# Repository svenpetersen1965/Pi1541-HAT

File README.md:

# Pi1541-HAT
Just another Pi1541-HAT. Please refer to Steve Whites project page (https://cbm-pi1541.firebaseapp.com/), who had the idea for the project and develops the software running in the Raspberry Pi.

There are several Pi1541-HATs, which are all good, nevertheless I have decided to make my own HAT. 

1. It has detachable display, switches and IEC-Bus boards

2. There is a barrel connector on the IEC-Bus Board, so no requirement for using the micro USB and no side entry for the enclosure required.

Find some info on the required cable making <a href="http://tech.guitarsite.de/cable_making.html">on my website</a>

I have made it this way to add flexibility to the HAT when it comes to be installed in an enclose and also alows a lower profile enclosure, since the high IEC-bus jacks are not above HAT level.

As a replacement for the switch board, a pcb with a rotary encoder with push button has been developed. This adds a quite bit more comfort while navigating through the directories. It mimiks the select, up and down button. This way, it works with the regular firmware (even before 1.21). Depending on the amount of text to be scrolled on the display, some pulses might get lost, which is hard to notice and does not reduce the usability.

The kernal revision v1.21 supports the connection of a rotary encoder. Rev. 2 of the HAT PCB provides the connection of a rotary encoder module (KY-040), which is widely available on ebay etc. This is ment to be as a cheaper alternative for the otary encoder board of this project. 

The Rev. 2 of HAT and Switch and the (newest) Rev. 1 of the IEC board were tested and are fully functional.

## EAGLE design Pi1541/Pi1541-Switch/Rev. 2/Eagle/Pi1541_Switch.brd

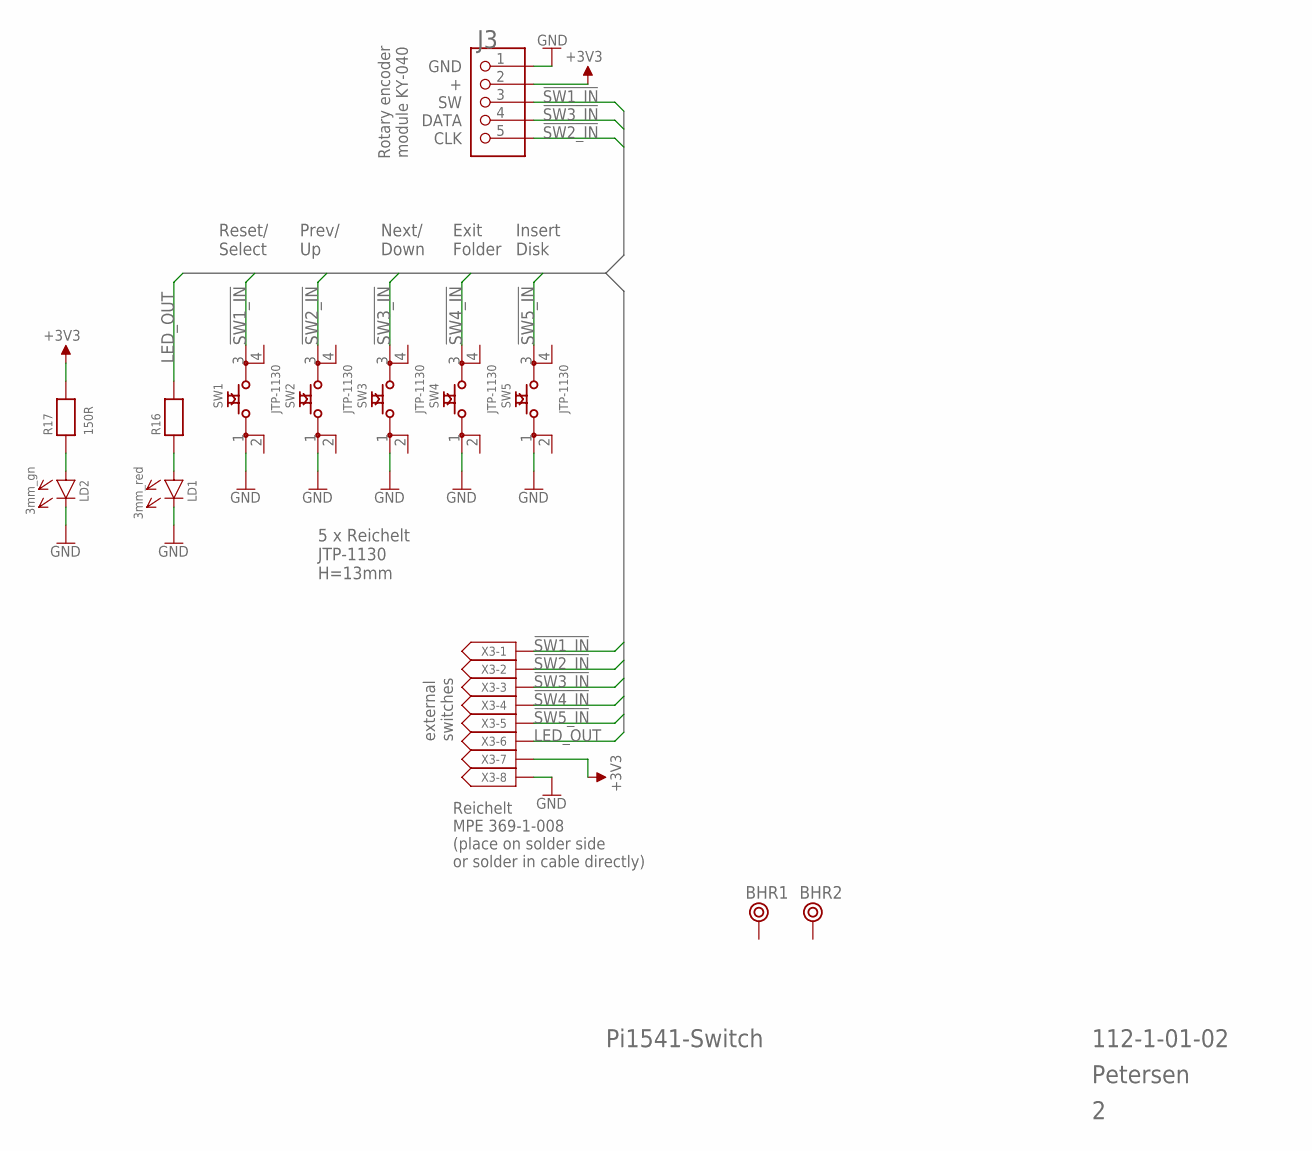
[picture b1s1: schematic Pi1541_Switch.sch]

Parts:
BHR1, BHR2: BOHR2,8; BOHR2,8_
J3: PINHD-1X5; 1X05
LD1: 3mm_red; 3MM
LD2: 3mm_gn; 3MM
R16, R17: 150R; 0805
SW1, SW2, SW3, SW4, SW5: JTP-1130
X3: MICMA08B

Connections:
!SW1_IN: J3.3, SW1.3, X3.1
!SW2_IN: J3.5, SW2.3, X3.2
!SW3_IN: J3.4, SW3.3, X3.3
!SW4_IN: SW4.3, X3.4
!SW5_IN: SW5.3, X3.5
+3V3: J3.2, R17.2, X3.7
GND: J3.1, LD1.C (K), LD2.C (K), SW1.1, SW2.1, SW3.1, SW4.1, SW5.1, X3.8
LED_OUT: R16.2, X3.6
unnamed: LD2.A, R17.1
unnamed: LD1.A, R16.1

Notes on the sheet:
5 x Reichelt JTP-1130 H=13mm
Reset/ Select
Prev/ Up
Next/ Down
Exit Folder
Insert Disk
external switches
Reichelt MPE 369-1-008 (place on solder side or solder in cable directly)
Pi1541-Switch
Petersen
112-1-01-02
GND
DATA
CLK
Rotary encoder module KY-040

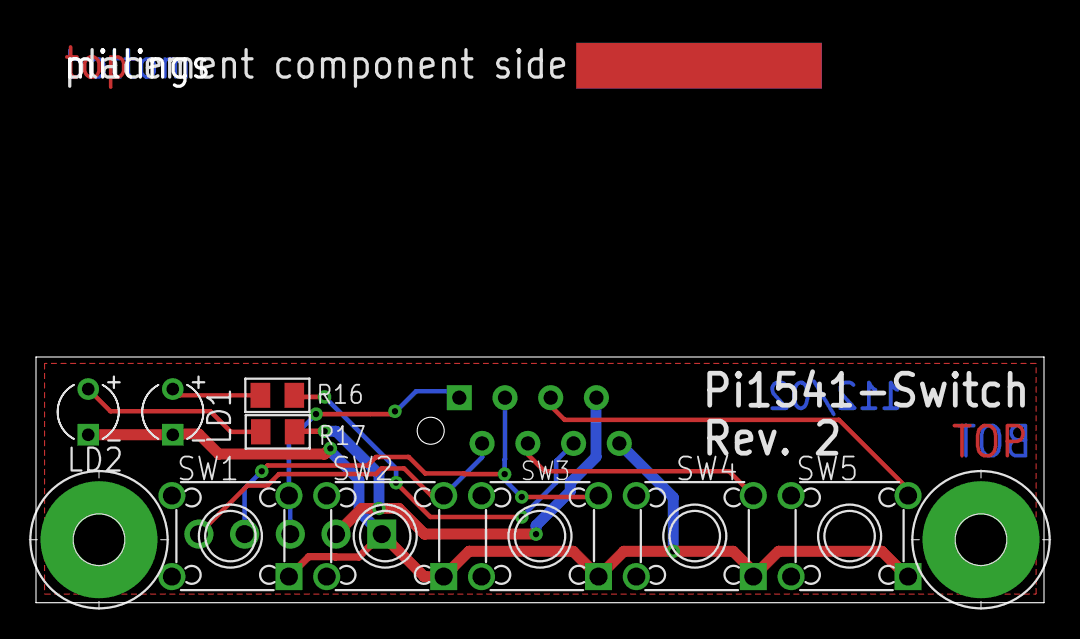
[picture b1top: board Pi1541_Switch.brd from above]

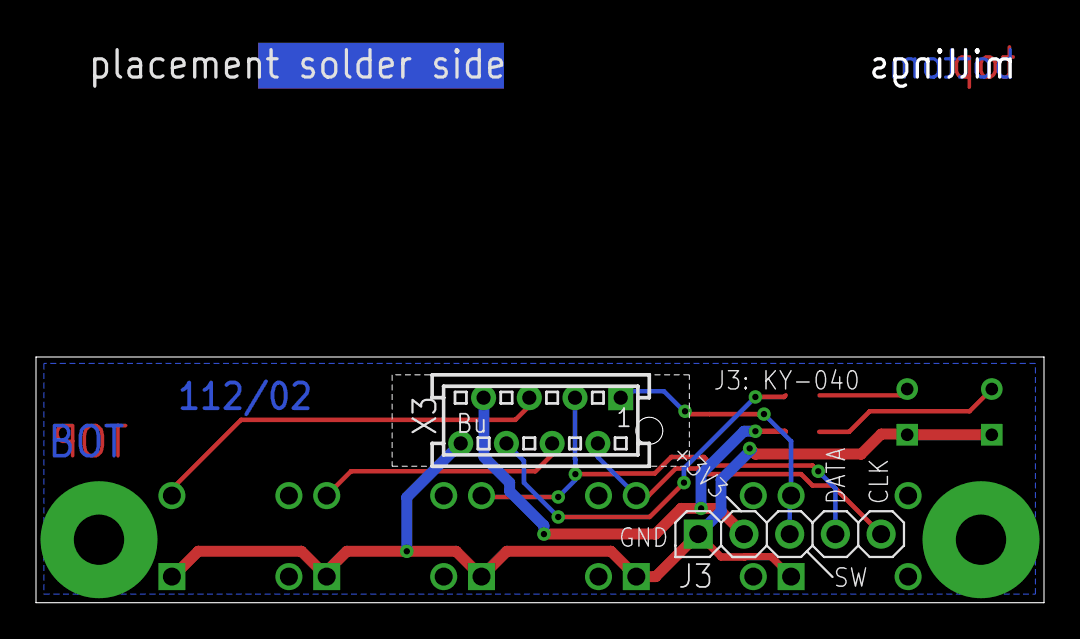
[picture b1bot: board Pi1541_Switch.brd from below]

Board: 2 copper layers, 56.0 x 31.5 mm, 15 parts (2 on the bottom side), 10 nets.

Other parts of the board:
U$44: 2LAYER
U$45: PCB-TITLE/

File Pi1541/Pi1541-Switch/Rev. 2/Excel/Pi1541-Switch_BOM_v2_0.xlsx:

Pi1541-Switch Rev. 2
Bill of Material Rev. 2.0
Pos. | Qty | Value | Footprint | Ref.-No. | Comment
1 | 1 | 112-2-01-02 | 2 Layers | PCB Rev. 2 | 2 layers, Cu 35µ, HASL, 13.65mm x 56.0mm, 1.6mm FR4
2 | 1 | 369-1-008 | MICMA08B | X3 | MPE Garry, Reichel MPE 369-1-008, Micromatch, female, tht, 8 pin
3 | 2 | 150R | 0805 | R16, R17 | resistor
4 | 1 | 3mm_gn | 3MM | LD2 | LED, 3mm, green
5 | 1 | 3mm_red | 3MM | LD1 | LED, 3mm, red
6 | 5 | JTP-1130D | JTP-1130 | SW1, SW2, SW3, SW4, SW5 | Namae Electronics, Reichelt JTP-1130, H=13mm
7 | 1 | 1x5p, pitch 2.54mm |  | J3 | Optional for rotary encoder (KY-040 etc.), standard pin header. Replaces SW1, S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
Pos. |  | Rev. 1 ® Rev. 2
1 |  | PCB revision
7 |  | new

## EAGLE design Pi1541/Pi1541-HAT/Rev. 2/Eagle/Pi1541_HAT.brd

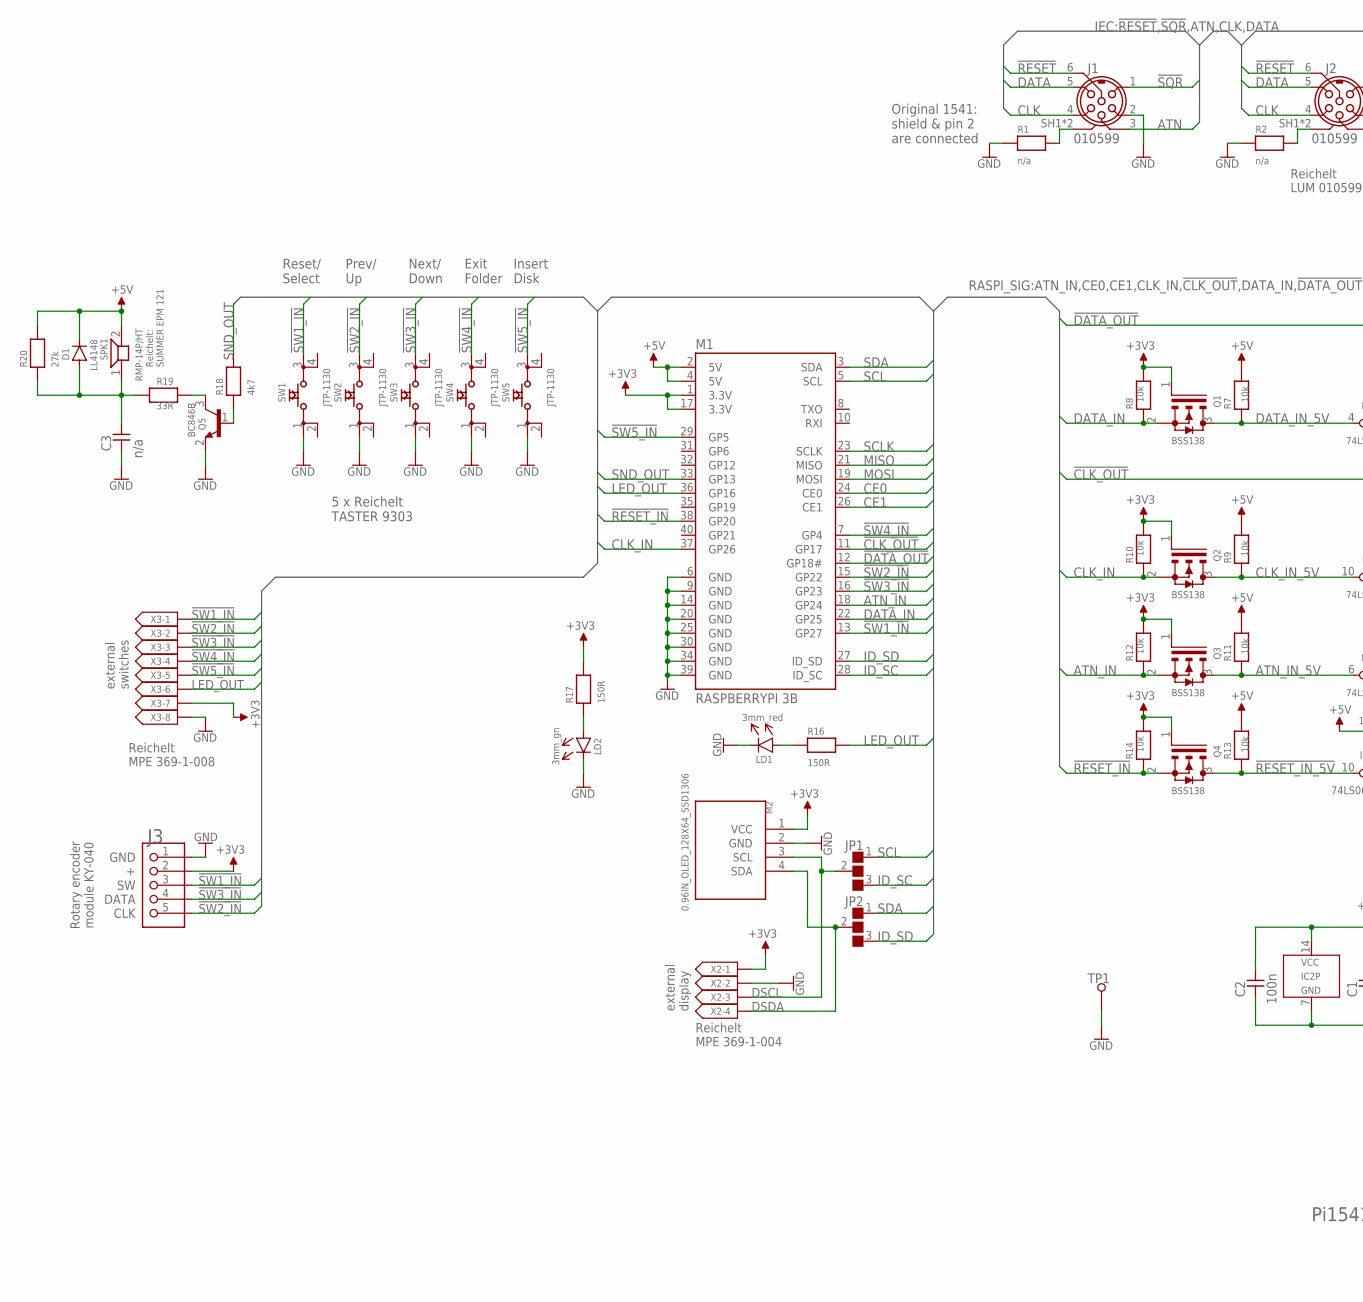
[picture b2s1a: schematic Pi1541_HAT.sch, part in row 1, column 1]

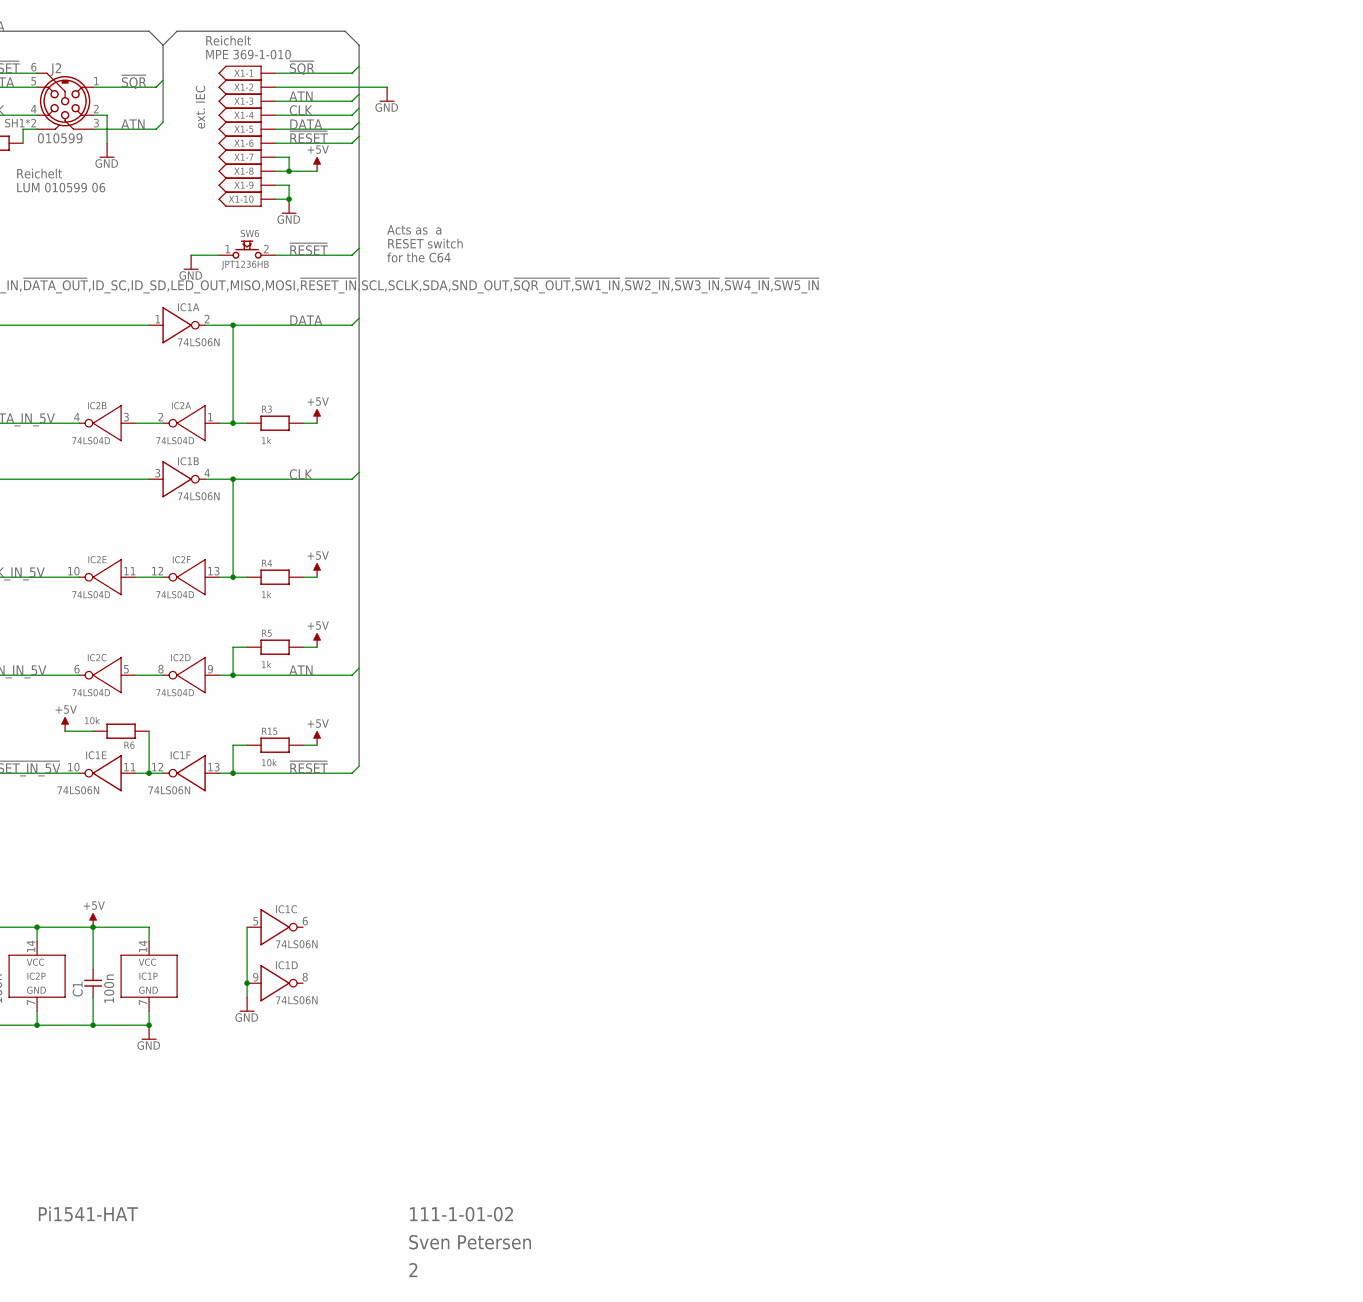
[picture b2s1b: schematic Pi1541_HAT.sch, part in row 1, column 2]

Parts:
C1, C2: 100n; 0805
C3: n/a; 0805
D1: LL4148; SOD80C
IC1: 74LS06N; DIL-14
IC2: 74LS04D; SO-14
J1, J2: 010599
J3: PINHD-1X5; 1X05
JP1, JP2: JMP_0603; CP3P
LD1: 3mm_red; 3MM
LD2: 3mm_gn; 3MM
M1: RASPBERRYPI 3B; PI_HAT_40P
M2: 0.96IN_OLED_128X64_SSD1306; OLED_0.96_SSD1306
Q1, Q2, Q3, Q4: BSS138; SOT23
Q5: BC846B; SOT23
R1, R2: n/a; 0805
R3, R4, R5: 1k; 0805
R6, R7, R8, R9, R10, R11, R12, R13, R14, R15: 10k; 0805
R16, R17: 150R; 0805
R18: 4k7; 0805
R19: 33R; 0805
R20: 27k; 0805
SPK1: RMP-14P/HT
SW1, SW2, SW3, SW4, SW5: JTP-1130
SW6: JPT1236HB; JTP_1236HB
TP1: L1,2_R; 1,2MM_R
X1: 369-1-010; MICMA10B
X2: 369-1-004; MICMA04B
X3: 369-1-008; MICMA08B

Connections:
!CLK_OUT: IC1.3 (I), M1.11 (GP17)
!DATA_OUT: IC1.1 (I), M1.12 (GP18#)
!RESET: IC1.13 (I), J1.6, J2.6, R15.1, SW6.2, X1.6
!RESET_IN: M1.38 (GP20), Q4.2 (S), R14.1
!RESET_IN_5V: IC1.10 (O), Q4.3 (D), R13.1
!SQR: J1.1, J2.1, X1.1
!SW1_IN: J3.3, M1.13 (GP27), SW1.3, X3.1
!SW2_IN: J3.5, M1.15 (GP22), SW2.3, X3.2
!SW3_IN: J3.4, M1.16 (GP23), SW3.3, X3.3
!SW4_IN: M1.7 (GP4), SW4.3, X3.4
!SW5_IN: M1.29 (GP5), SW5.3, X3.5
+3V3: J3.2, M1.1 (3.3V), M1.17 (3.3V), M2.1 (VCC), Q1.1 (G), Q2.1 (G), Q3.1 (G), Q4.1 (G), R8.2, R10.2, R12.2, R14.2, R17.2, X2.1, X3.7
+5V: C1.2, C2.2, D1.K, IC1.14 (VCC), IC2.14 (VCC), M1.2 (5V), M1.4 (5V), R3.2, R4.2, R5.2, R6.2, R7.2, R9.2, R11.2, R13.2, R15.2, R20.2, SPK1.2, X1.7, X1.8
ATN: IC2.9 (I), J1.3, J2.3, R5.1, X1.3
ATN_IN: M1.18 (GP24), Q3.2 (S), R12.1
ATN_IN_5V: IC2.6 (O), Q3.3 (D), R11.1
CE0: M1.24 (CE0)
CE1: M1.26 (CE1)
CLK: IC1.4 (O), IC2.13 (I), J1.4, J2.4, R4.1, X1.4
CLK_IN: M1.37 (GP26), Q2.2 (S), R10.1
CLK_IN_5V: IC2.10 (O), Q2.3 (D), R9.1
DATA: IC1.2 (O), IC2.1 (I), J1.5, J2.5, R3.1, X1.5
DATA_IN: M1.22 (GP25), Q1.2 (S), R8.1
DATA_IN_5V: IC2.4 (O), Q1.3 (D), R7.1
DSCL: JP1.2, M2.3 (SCL), X2.3
DSDA: JP2.2, M2.4 (SDA), X2.4
GND: C1.1, C2.1, C3.1, IC1.5 (I), IC1.7 (GND), IC1.9 (I), IC2.7 (GND), J1.2, J2.2, J3.1, LD1.K, LD2.K, M1.6 (GND), M1.9 (GND), M1.14 (GND), M1.20 (GND), M1.25 (GND), M1.30 (GND), M1.34 (GND), M1.39 (GND), M2.2 (GND), Q5.2 (E), R1.1, R2.1, SW1.1, SW2.1, SW3.1, SW4.1, SW5.1, SW6.1, TP1.1, X1.2, X1.9, X1.10, X2.2, X3.8
ID_SC: JP1.3, M1.28 (ID_SC)
ID_SD: JP2.3, M1.27 (ID_SD)
LED_OUT: M1.36 (GP16), R16.2, X3.6
MISO: M1.21 (MISO)
MOSI: M1.19 (MOSI)
unnamed: J1.SH1 (SH), J1.SH2 (SH), R1.2
unnamed: J2.SH1 (SH), J2.SH2 (SH), R2.2
unnamed: IC2.2 (O), IC2.3 (I)
unnamed: IC2.11 (I), IC2.12 (O)
unnamed: IC2.5 (I), IC2.8 (O)
unnamed: IC1.11 (I), IC1.12 (O), R6.1
unnamed: LD2.A, R17.1
unnamed: Q5.1 (B), R18.1
unnamed: Q5.3 (C), R19.2
unnamed: C3.2, D1.A, R19.1, R20.1, SPK1.1
unnamed: LD1.A, R16.1
SCL: JP1.1, M1.5 (SCL)
SCLK: M1.23 (SCLK)
SDA: JP2.1, M1.3 (SDA)
SND_OUT: M1.33 (GP13), R18.2

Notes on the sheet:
Original 1541: shield & pin 2 are connected
5 x Reichelt TASTER 9303
Reset/ Select
Prev/ Up
Next/ Down
Exit Folder
Insert Disk
Reichelt: SUMMER EPM 121
external display
external switches
Acts as a RESET switch for the C64
Reichelt MPE 369-1-004
Reichelt MPE 369-1-008
Reichelt MPE 369-1-010
ext. IEC
Reichelt LUM 010599 06
Pi1541-HAT
Sven Petersen
111-1-01-02
GND
DATA
CLK
Rotary encoder module KY-040

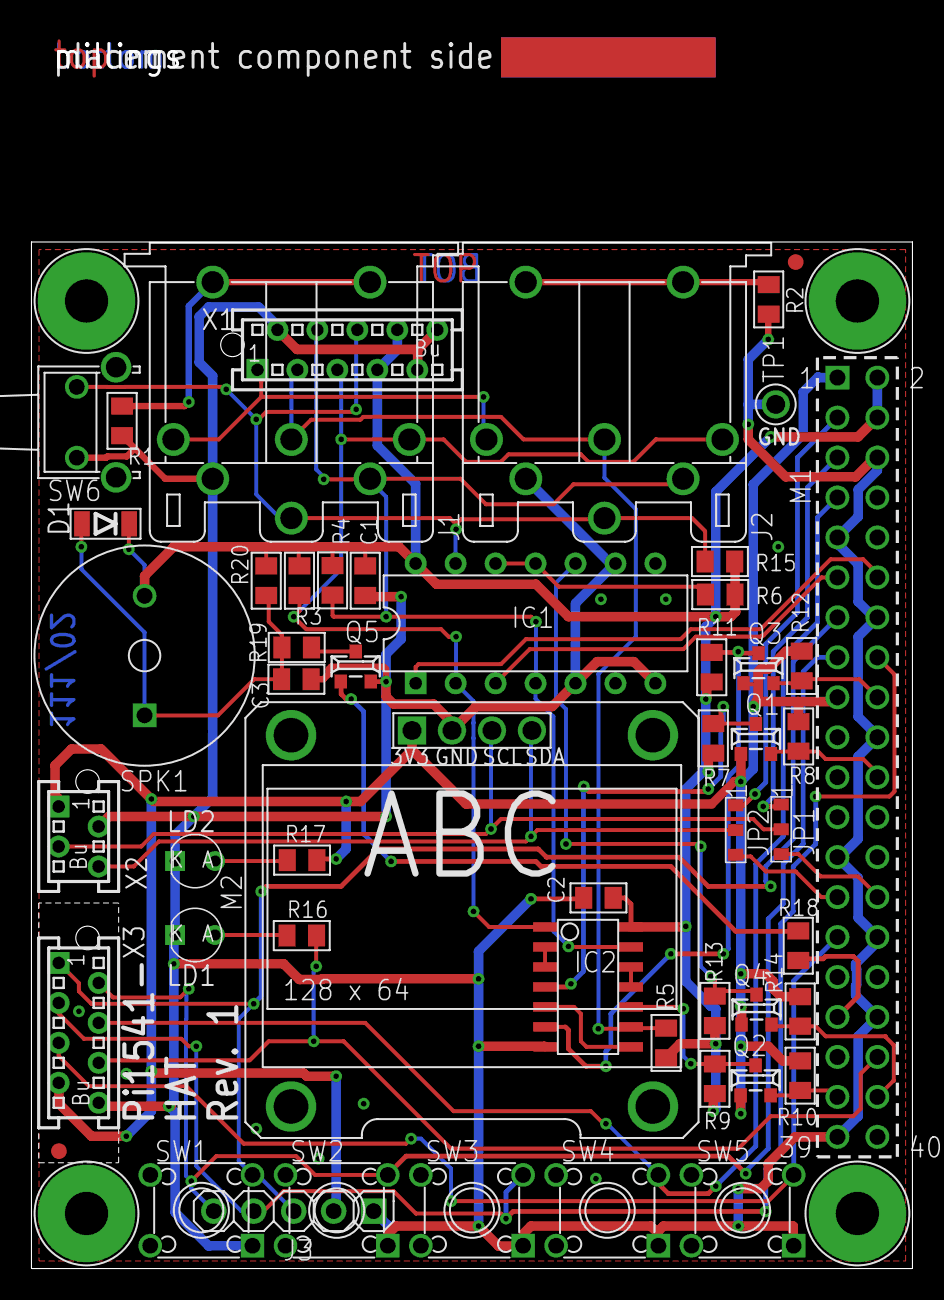
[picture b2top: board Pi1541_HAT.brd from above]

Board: 2 copper layers, 56.0 x 78.6 mm, 55 parts (0 on the bottom side), 42 nets.

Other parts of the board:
U$44: 2LAYER
U$45: PCB-TITLE/
U$47, U$48: SMD_REF_R1MM

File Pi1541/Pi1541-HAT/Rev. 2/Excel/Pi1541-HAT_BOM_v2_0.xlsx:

Pi1541-HAT Rev. 2
Bill of Material Rev. 2.0
Pos. | Qty | Value | Footprint | Ref.-No. | Comment
1 | 1 | 111-2-01-02 | 2 Layer | PCB Rev. 2 | 2 layer, Cu 35µ, HASL, 56.0mm x 65.25mm, 1.6mm FR4
2 | 1 | 369-1-008 | MICMA08B | X3 | MicroMatch MPE, e.g. Reichelt MPE 369-1-008
3 | 1 | 372-1-008 |  | (X3) | option: MicroMatch MPE, e.g. Reichelt MPE 372-1-008
4 | 1 | 0.96IN_OLED_128X64_SSD1306 | OLED_0.96_SSD1306 | M2 | 0.96" OLED Display 128x64, controller: SSD1306 or 1.3" OLED Display 128x64, con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
5 | 1 | 115-1-004 |  | (M2) | option: MPE Garry, e.g. Reichelt MPE 115-1-004
6 | 2 | 010599 | 10599 | J1, J2 | Lumberg, e.g. Reichelt 010599 06
7 | 3 | 100n | 0805 | C1, C2, C3
8 | 10 | 10k | 0805 | R6, R7, R8, R9, R10, R11, R12, R13, R14, R15
9 | 2 | 150R | 0805 | R16, R17
10 | 3 | 1k | 0805 | R3, R4, R5
11 | 1 | 33R | 0805 | R19
12 | 1 | 3mm_gn | 3MM | LD2 | LED 3mm, green
13 | 1 | 3mm_red | 3MM | LD1 | LED 3mm, red
14 | 1 | 74LS04D | SO-14 | IC2
15 | 1 | 74LS06N | DIL-14 | IC1
16 | 1 | BC846B | SOT23 | Q5
17 | 4 | BSS138 | SOT23 | Q1, Q2, Q3, Q4
18 | 2 | JMP_0603 | CP3P | JP1, JP2 | Jumper, default: 0R/0603 (1-2)
19 | 2 | 0R | 0603 | (JP1), (JP2)
20 | 1 | JPT1236HB | JTP_1236HB | SW6 | Namae Electronics, e.g. Reichelt TASTER 3305B
21 | 5 | JTP-1130 | JTP-1130 | SW1, SW2, SW3, SW4, SW5 | Namae Electronics, e.g. Reichelt TASTER 9303
22 | 1 | LL4148 | SOD80C | D1 | Diode
23 | 1 | 369-1-004 | MICMA04B | X2 | MicroMatch MPE, e.g. Reichelt MPE 369-1-004
24 | 1 | 372-1-004 |  | (X2) | option: MicroMatch MPE, e.g. Reichelt MPE 372-1-004
25 | 1 | 369-1-010 | MICMA06B | X1 | MicroMatch MPE, e.g. Reichelt MPE 369-1-010
26 | 1 | 372-1-010 |  | (X1) | option: MicroMatch MPE, e.g. Reichelt MPE 372-1-010
27 | 1 | RASPBERRYPI 3B |  | M1 | Raspberry Pi 3B or better
28 | 1 | MPE 094-2-040 |  | (M1) | MPE, e.g. Reichelt MPE 094-2-040
29 | 1 | RMP-14P/HT | RMP-14P/HT | SPK1 | KM, e.g. Reichelt SUMMER EPM 121
30 | 1 | 4k7 | 0805 | R18
31 | 2 | dnp | 0805 | R1, R2 | option 0R, not placed
32 | 1 | 27k | 0805 | R20
33 | 1 | 1.3mm/2mm |  | TP1 | not assembled
34 | 1 | 1x5p, 2.54mm | 1x5 | J3 | option: for rotary encoder, replaces SW1 to SW3, straight or 90°
35 | 1 | KY-040 |  | (J3) | option: rotary encoder module.
36 | 1 | DuPont wire (5 wires) |  |  | optional for the rotary encoder module
Pos. |  | Rev. 1 ® Rev. 2
1 |  | PCB revision
34 |  | new, option
35 |  | new, option
36 |  | new, option

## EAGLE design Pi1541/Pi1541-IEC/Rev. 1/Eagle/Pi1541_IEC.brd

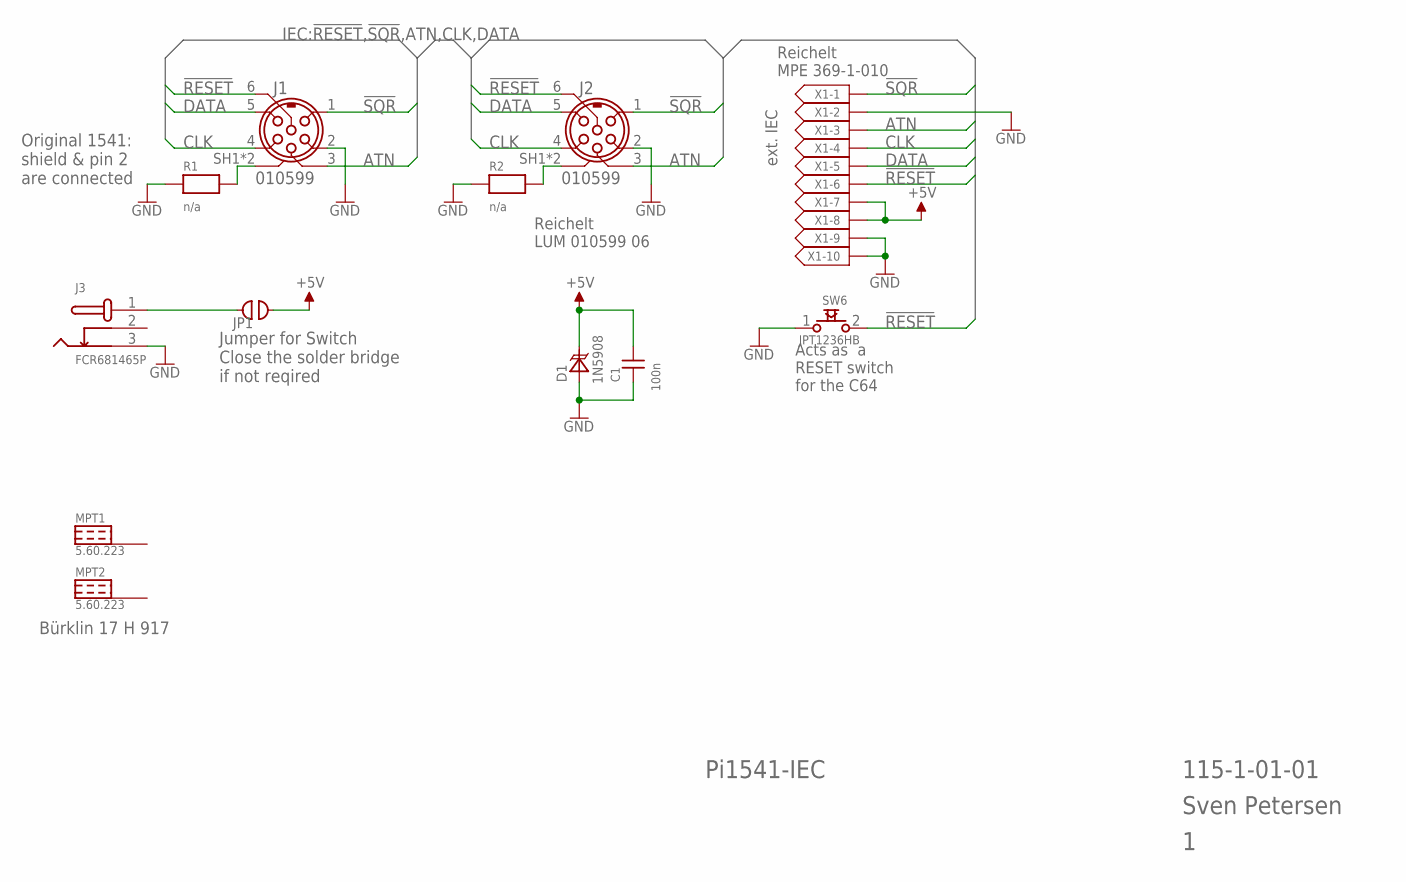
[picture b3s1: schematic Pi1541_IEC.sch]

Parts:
C1: 100n; C-2,5
D1: 1N5908; CB429
J1, J2: 010599
J3: FCR681465P
JP1: COMBI_2P; COMBI-2P
MPT1, MPT2: 5.60.223
R1, R2: n/a; 0805
SW6: JPT1236HB; JTP_1236HB
X1: 369-1-010; MICMA10B

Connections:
!RESET: J1.6, J2.6, SW6.2, X1.6
!SQR: J1.1, J2.1, X1.1
+5V: C1.2, D1.K, JP1.2, X1.7, X1.8
ATN: J1.3, J2.3, X1.3
CLK: J1.4, J2.4, X1.4
DATA: J1.5, J2.5, X1.5
GND: C1.1, D1.A, J1.2, J2.2, J3.3, R1.1, R2.1, SW6.1, X1.2, X1.9, X1.10
unnamed: J1.SH1 (SH), J1.SH2 (SH), R1.2
unnamed: J2.SH1 (SH), J2.SH2 (SH), R2.2
unnamed: J3.1, JP1.1

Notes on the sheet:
Original 1541: shield & pin 2 are connected
Acts as a RESET switch for the C64
Reichelt MPE 369-1-010
ext. IEC
Reichelt LUM 010599 06
Pi1541-IEC
Sven Petersen
115-1-01-01
Bürklin 17 H 917
Jumper for Switch Close the solder bridge if not reqired

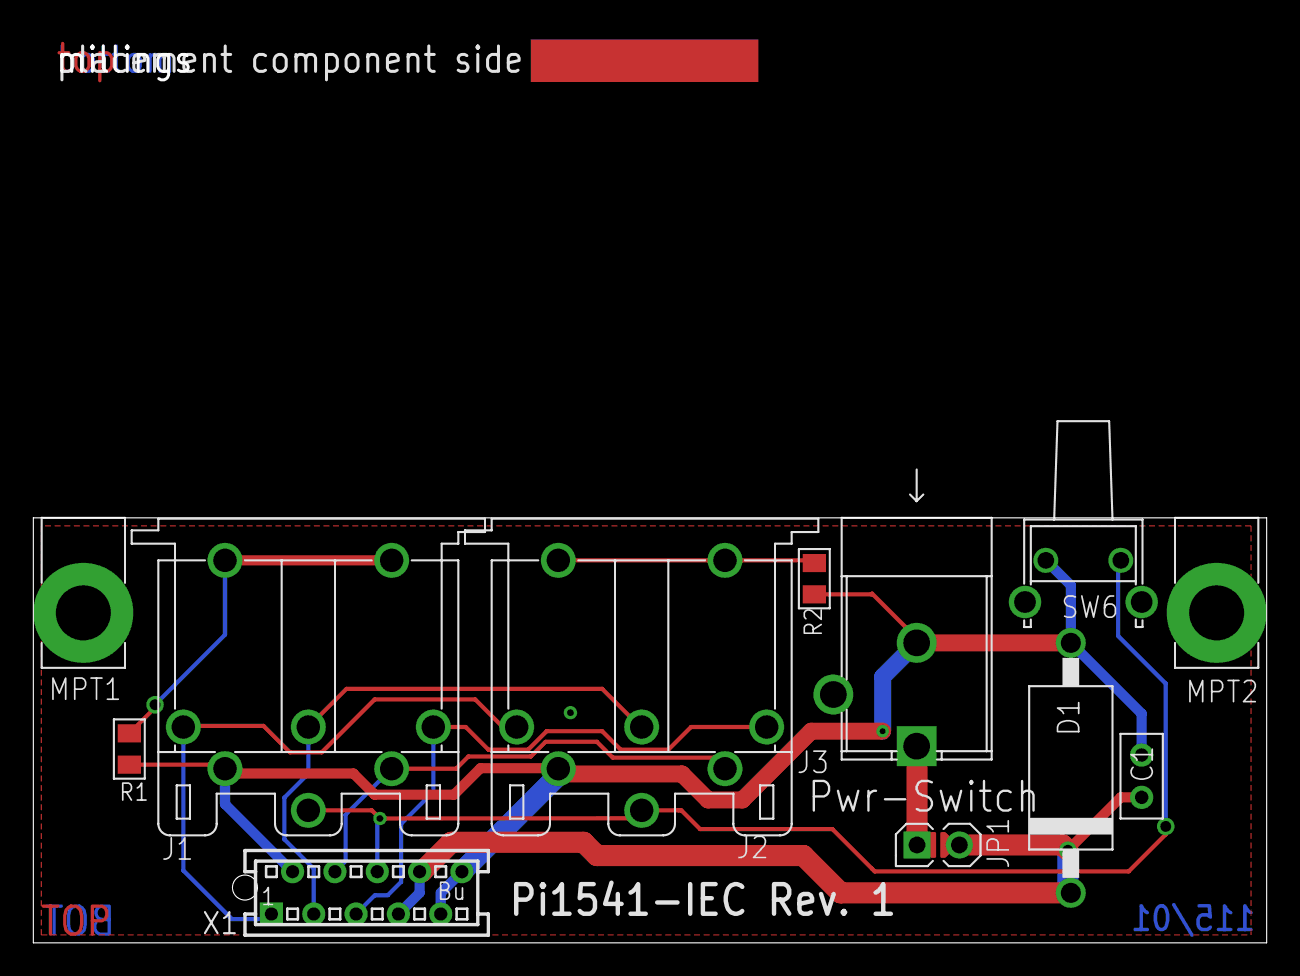
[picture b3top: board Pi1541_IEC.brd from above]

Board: 2 copper layers, 74.0 x 54.6 mm, 14 parts (0 on the bottom side), 10 nets.

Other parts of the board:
U$44: 2LAYER
U$45: PCB-TITLE/

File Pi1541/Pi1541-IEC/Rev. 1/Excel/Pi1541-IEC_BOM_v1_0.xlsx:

Pi1541-IEC Rev. 1
Bill of Material Rev. 1.0
Pos. | Qty | Value | Footprint | Ref.-No. | Comment
1 | 1 | 115-2-01-01 | 2 Layer | PCB Rev. 1 | 2 layer, Cu 35µ, HASL, 71.0mm x 25.5mm, 1.6mm FR4
2 | 2 | 10599 | 10599 | J1, J2 | Lumberg, e.g. Reichelt 010599 06, tme.eu: 0105-06
3 | 1 | 100n | C-2,5 | C1 | ceramic capacitor, pitch: 2.5mm
4 | 1 | 1N5908 | CB429 | D1 | TVS Diode (5V)
5 | 1 | 369-1-010 | MICMA10B | X1 | MicroMatch MPE, e.g. Reichelt MPE 369-1-010, tme.eu 1-215079-0/C
6 | 1 | 372-1-010 |  | (X1) | MicroMatch MPE, e.g. Reichelt MPE 372-1-010, tme.eu: 1-215083-0/C
6 | 2 | 5.60.223 | 5.60.223 | MPT1, MPT2 | Ettinger, e.g. Bürklin 17 H 917 (optional for mounting)
7 | 1 | FCR681465P | FCR681465P | J3 | Cliff, Reichelt: CLIFF FCR681465P, tme.eu: FCR681465P
8 | 1 | JPT1236HB | JTP_1236HB | SW6 | Namae Electronics, e.g. Reichelt TASTER 3305B, tme.eu: TACTA-68N-F
9 | 2 | n/a | 0805 | R1, R2 | not assembled
10 | 1 | jumper 2.54mm |  | JP1 | optional for connecting power switch
 |  | Rev. 0 ® Rev. 1
Pos. | 1 | PCB revision
Pos. | 10 | new

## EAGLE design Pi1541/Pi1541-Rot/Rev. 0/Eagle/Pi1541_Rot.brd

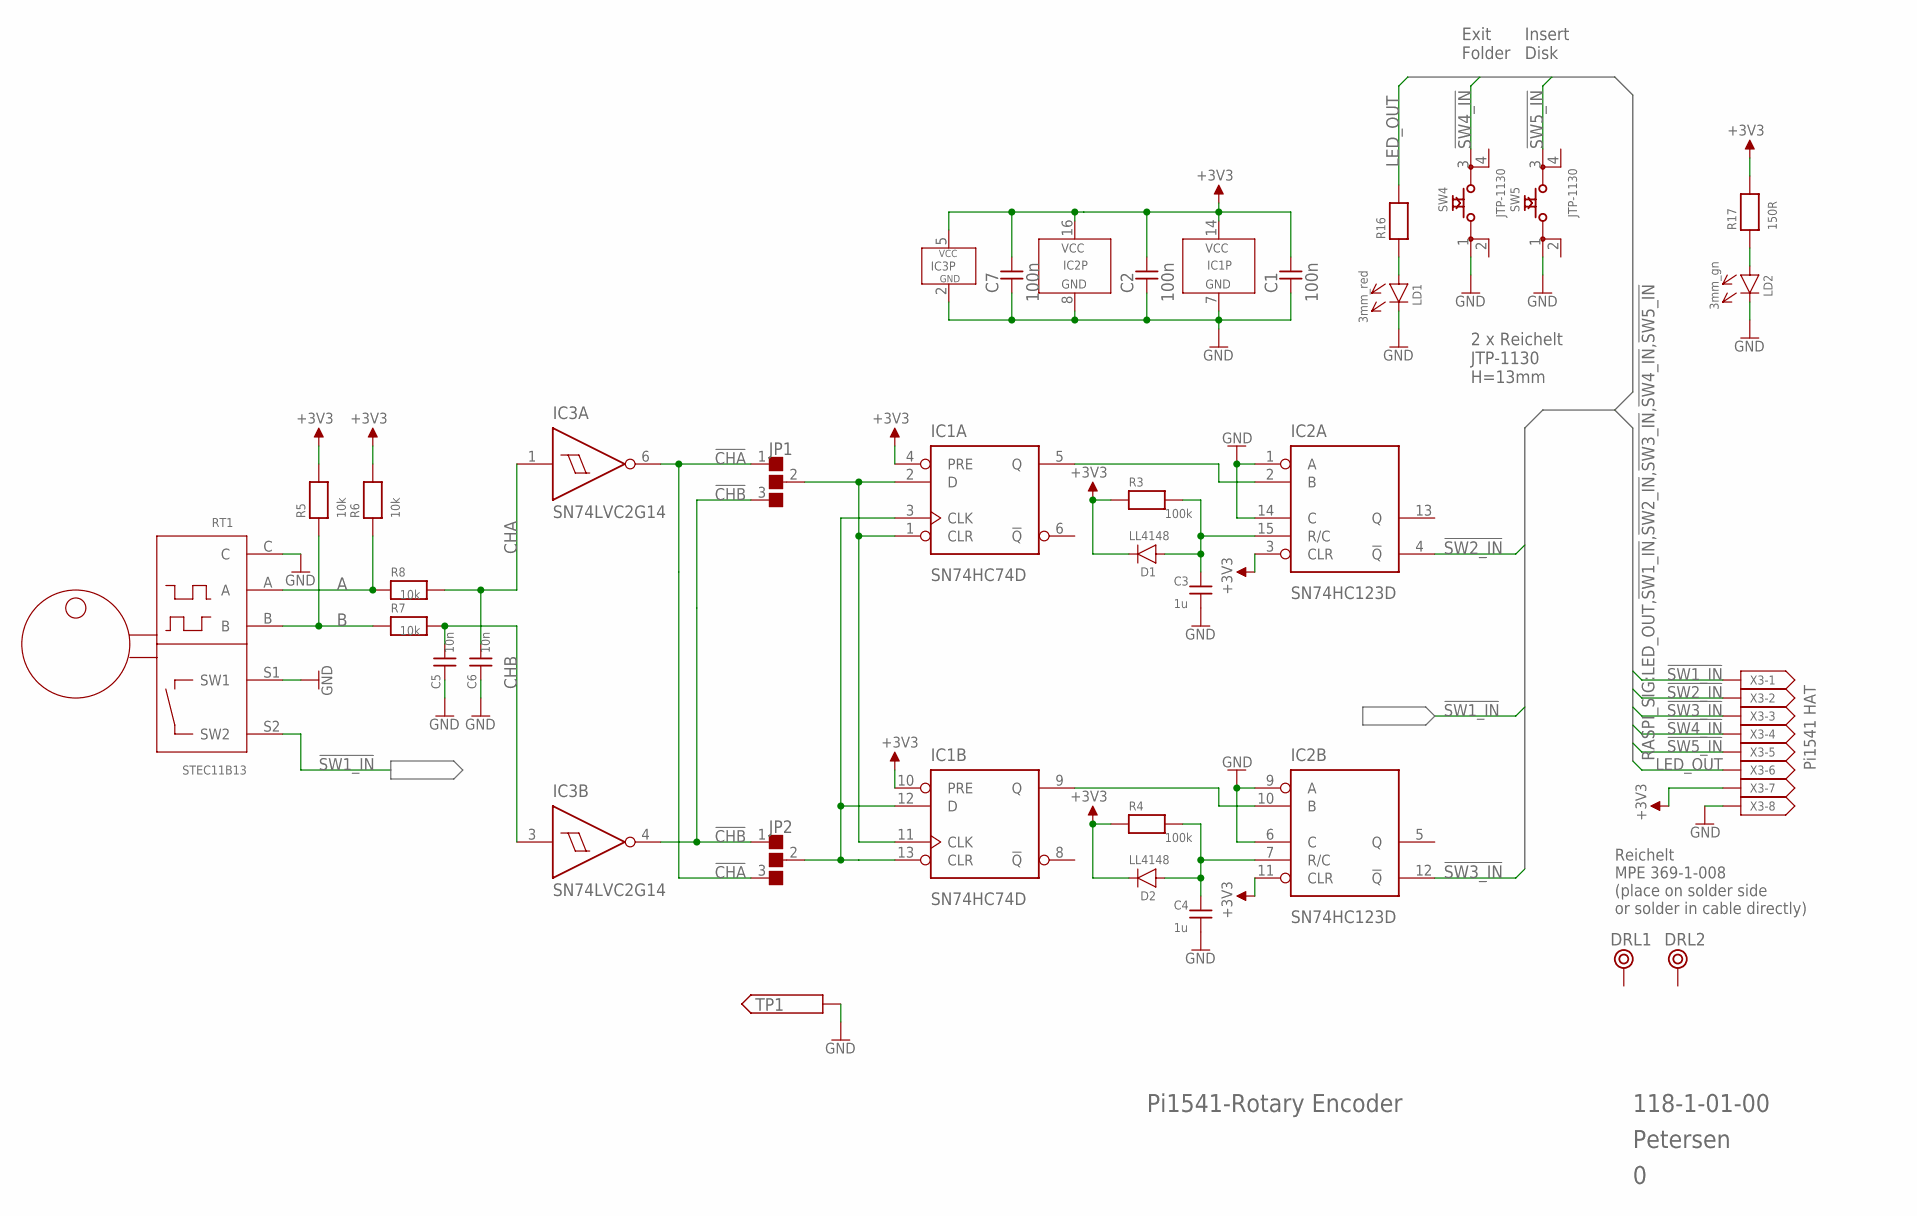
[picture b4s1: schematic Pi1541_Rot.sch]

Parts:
C1, C2, C7: 100n; 0805
C3, C4: 1u; 0805
C5, C6: 10n; 0805
D1, D2: LL4148; SOD80C
DRL1, DRL2: BOHR2,8; BOHR2,8_
IC1: SN74HC74D; SO-14
IC2: SN74HC123D; SO-16
IC3: SN74LVC2G14; SOT23-6
JP1, JP2: JMP_0603; CP3P
LD1: 3mm_red; 3MM
LD2: 3mm_gn; 3MM
R3, R4: 100k; 0805
R5, R6, R7, R8: 10k; 0805
R16, R17: 150R; 0805
RT1: STEC11B13
SW4, SW5: JTP-1130
TP1: PAD1,0/AUTO; 1.0/AUTO
X3: MICMA08B

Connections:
!CHA: IC3.6 (O), JP1.1, JP2.3
!CHB: IC3.4 (O), JP1.3, JP2.1
!SW1_IN: RT1.S2 (SW2), X3.1
!SW2_IN: IC2.4 (!Q), X3.2
!SW3_IN: IC2.12 (!Q), X3.3
!SW4_IN: SW4.3, X3.4
!SW5_IN: SW5.3, X3.5
+3V3: C1.2, C2.2, C7.2, D1.K, D2.K, IC1.4 (PRE), IC1.10 (PRE), IC1.14 (VCC), IC2.3 (CLR), IC2.11 (CLR), IC2.16 (VCC), IC3.5 (VCC), R3.1, R4.1, R5.2, R6.2, R17.2, X3.7
A: R6.1, R8.1, RT1.A
B: R5.1, R7.1, RT1.B
CHA: C6.2, IC3.1 (I), R8.2
CHB: C5.2, IC3.3 (I), R7.2
GND: C1.1, C2.1, C3.2, C4.2, C5.1, C6.1, C7.1, IC1.7 (GND), IC2.1 (A), IC2.6 (C), IC2.8 (GND), IC2.9 (A), IC2.14 (C), IC3.2 (GND), LD1.C (K), LD2.C (K), RT1.C, RT1.S1 (SW1), SW4.1, SW5.1, TP1.1, X3.8
LED_OUT: R16.2, X3.6
unnamed: IC1.5 (Q), IC2.2 (B)
unnamed: IC1.9 (Q), IC2.10 (B)
unnamed: IC1.1 (CLR), IC1.2 (D), IC1.11 (CLK), JP1.2
unnamed: C3.1, D1.A, IC2.15 (R/C), R3.2
unnamed: C4.1, D2.A, IC2.7 (R/C), R4.2
unnamed: IC1.3 (CLK), IC1.12 (D), IC1.13 (CLR), JP2.2
unnamed: LD2.A, R17.1
unnamed: LD1.A, R16.1

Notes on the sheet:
2 x Reichelt JTP-1130 H=13mm
Exit Folder
Insert Disk
Pi1541 HAT
Reichelt MPE 369-1-008 (place on solder side or solder in cable directly)
Pi1541-Rotary Encoder
Petersen
118-1-01-00

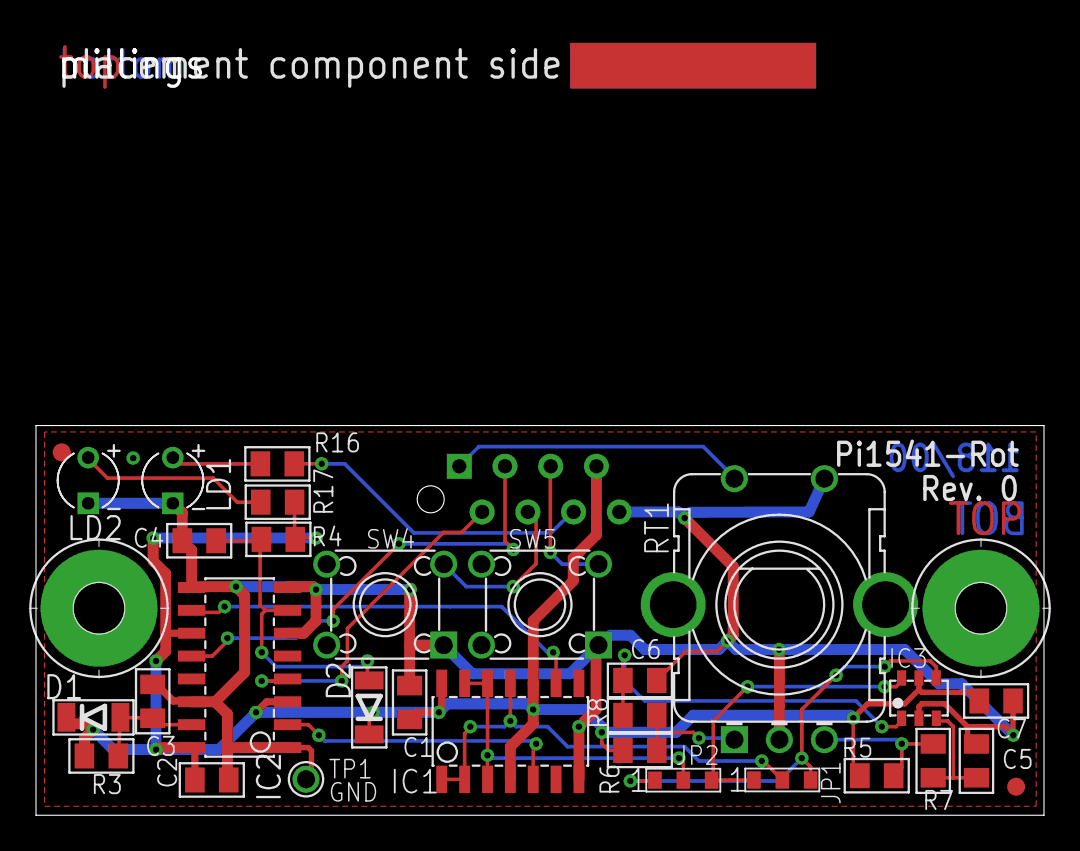
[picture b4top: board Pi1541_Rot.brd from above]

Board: 2 copper layers, 56.0 x 43.3 mm, 35 parts (1 on the bottom side), 22 nets.

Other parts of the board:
U$23, U$24: SMD_REF_R1MM
U$44: 2LAYER
U$45: PCB-TITLE/

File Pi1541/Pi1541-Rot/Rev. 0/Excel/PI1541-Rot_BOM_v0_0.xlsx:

Pi1541-Rotary Encoder Board Rev. 0
Bill of Material Rev. 0.0
Pos. | Qty | Value | Footprint | Ref.-No. | Comment
1 | 1 | 118-2-01-00 | 2 Layer | PCB Rev. 0 | 2 layer, Cu 35µ, HASL, LLL x BBB, 1.6mm FR4
2 | 1 | 369-1-008 | MICMA08B | X3 | MPE Garry, Reichel MPE 369-1-008, Micromatch, female, tht, 8 pin
3 | 3 | 100n | 0805 | C1, C2, C7 | cer cap 0805
4 | 4 | 10k | 0805 | R5, R6, R7, R8 | resistor 0805, 5% or better
5 | 2 | 10n | 0805 | C5, C6 | cer cap 0805
6 | 2 | 150R | 0805 | R16, R17 | resistor 0805, 5% or better
7 | 2 | 150k | 0805 | R3, R4 | resistor 0805, 5% or better
8 | 2 | 1u | 0805 | C3, C4 | cer cap 0805, e.g. Reichelt X7R 1206 BF 1,0U
9 | 1 | 3mm_gn | 3MM | LD2 | LED, 3mm, green, e.g. Reichelt LED 3MM GN
10 | 1 | 3mm_red | 3MM | LD1 | LED, 3mm, red, e.g. Reichelt LED 3MM RT
11 | 2 | JMP_0603 | CP3P | JP1, JP2 | Jumper (in copper, no sourcable part), 0R resistor (0603) placed 1-2 by default
12 | 1 | 0R | 603 | (JP1), (JP2) | resistor 0603, placed on SMD jumper, e.g. Reichelt RND 0603 0
13 | 2 | JTP-1130 | JTP-1130 | SW4, SW5 | Namae Electronics, Reichelt JTP-1130, H=13mm
14 | 2 | LL4148 | SOD80C | D1, D2 | Diode, MINIMELF
15 | 1 | SN74HC123D | SO-16 | IC2 | e.g. TI, Toshiba, etc. Reichelt: SMD HC 123
16 | 1 | SN74HC74D | SO-14 | IC1 | e.g. NXP, Reichelt: SMD HC 74
17 | 1 | knob for rotary axis 6 mm |  | (RT1) | e.g. Reichelt KNOPF 10-150B
18 | 1 | STEC11B13 | STEC11B13 | RT1 | Alps, Reichelt: STEC11B13
19 | 2 | n/a | 0805 | R1, R2 | not assembled
20 | 1 | SN74LVC2G14 | SOT23-6 | IC3 | TI, e.g. Reichelt SN 74LVC2G14DBV

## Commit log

2019-03-17 Initial Upload
2019-03-17 More text and a picture
2019-03-17 added the url of steve white's website
2019-03-18 Addendum Prototype Testing
    I have found something out.
2019-03-18 Addendum Prototype testing
    I found out, how flipping disks works...
2019-04-08 Now new: Rotary encoder option
    The Pi1541 can work with a rotary encoder instead of the Pi1541 Switch board. The original firmware works, since the circuit mimiks the original switches.
2019-04-08 Added a picture of the rotary encoder board
2019-11-03 Add files via upload
    Added a pin header to connect a power switch
2019-11-29 Revision 2 (rotary encoder support)
2019-11-30 Add files via upload
    Rev. 2 released, this sopports the connection of a rotary encoder module, like KY-040. A standard rotary encoder is supported after firmware/kernel version v1.21
